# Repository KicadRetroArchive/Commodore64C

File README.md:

# Commodore 64C KiCad schematics

This project contains a series of schematics and PCB designs for the
Commodore 64C (aka C64-E) personal computer, redrawn in [KiCad](https://kicad.org/).

The schematic was extracted from images available from
[Bo Zimmerman's FTP site](http://www.zimmers.net/anonftp/pub/cbm/schematics/computers/c64/index.html).

The images are also available in the documentation directory.

The project is structured in three main folders:

- [250469-RevA](250469-RevA) - Revision A of the motherboard. This version is also known as
  _Short Board_ and sports the 64 pin _"Super PLA"_ (code 251715-01).
- [250469-RevB](250469-RevB) - Revision B of the motherboard. This version has
  a more advanced version of the Super PLA (code 252535-01) that integrates the Color RAM.
- [docs](docs) - Documentation.
- [libs](libs) - Project's specific KiCad libraries.

## References

- Schematics from [Zimmers FTP site](http://www.zimmers.net/anonftp/pub/cbm/schematics/computers/c64/index.html).
- [C64C Service Manual](http://www.zimmers.net/anonftp/pub/cbm/schematics/computers/c64/servicemanuals/C64-C64C_Service_Manual_314001-03_%281992_Mar%29.pdf).
- [Hardware information](https://www.c64-wiki.com/wiki/Portal:Hardware) from the C64-Wiki.

## Differences

While designing the schematics, I decided to consider the availability of all the
components used as a top priority. While there's little I can do for many of the
ICs, many other components can still be sourced from distributors today.

A few regular components are, however, impossible to find now. In these cases
I replaced them with the closest substitute I could find that is widely available.
These components are different from the originals:

- `CR2`: Diode Rectifier Bridge
- `L3,L4`: RF Choke Coils
- Some transistors and diodes

## KiCad libraries

Both subprojects use two KiCad set of libraries:

- The [KiCad Retro Library](https://github.com/KicadRetroArchive/kicad-retro-library).
- Project-specific libraries located in the [libs](libs) directory.
  - `C64-C-250469.kicad_sym` - C64C specific symbols.
  - `C64-C-250469.pretty` - C64C specific footprints.

> The project-specific libraries are located in a directory **above** the actual
> KiCad project. They are referenced through the `KIPRJMOD` environment variable
> in this way: `"${KIPRJMOD}/../libs/<name of library>"`.

## Credits

This project has been heavily inspired by these awesome projects:

- [LittleSixteen](https://github.com/SukkoPera/LittleSixteen) - Clone of the Commodore 16 by [@SukkoPera](https://github.com/SukkoPera).
- [Commodore-Plus4](https://github.com/StormTrooper/Commodore-Plus4) - Clone of the Commodore Plus 4 by [@StormTrooper](https://github.com/StormTrooper).
- [KU-14194HB-RevB-KiCad](https://github.com/bwack/KU-14194HB-RevB-KiCad) - Clone of the Commodore 64, Assy KU-14194HB-RevB by [@bwack](https://github.com/bwack).

## Contributing

We gladly accept contributions via GitHub pull requests. Please see
[CONTRIBUTING.md](CONTRIBUTING.md) for more details.

## License

Original schematic drawings and service manual are &copy; Commodore Electronics Ltd.

All KiCad design files are copyright &copy; 2020 Andrea Cisternino.

This project is Open Hardware licensed under the
[CERN-OHL-S v2](https://ohwr.org/project/cernohl/wikis/Documents/CERN-OHL-version-2)
license.

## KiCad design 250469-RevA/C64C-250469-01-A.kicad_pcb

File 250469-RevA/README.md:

# Assembly 250469 Rev. A

Original board:

(_From the [C64-Wiki](https://www.c64-wiki.com/wiki/Motherboard)_)

## Files

- Schematics in PDF: [C64C-250469-01-A.pdf](C64C-250469-01-A.pdf)
- Complete BOM in LibreOffice Calc format, including part numbers from Digi-Key and Mouser
  [C64C-250469-01-A.ods](C64C-250469-01-A.ods)

## Status

I am quite confident that the schematic is stable and bug-free.

**Good News!** I acquired a spare motherboard that matches exactly this revision.
With this example in my hand, I corrected all dimensional errors in the PCB.
I also placed with great precision all the external connectors.
Now work on routing the PCB can begin!

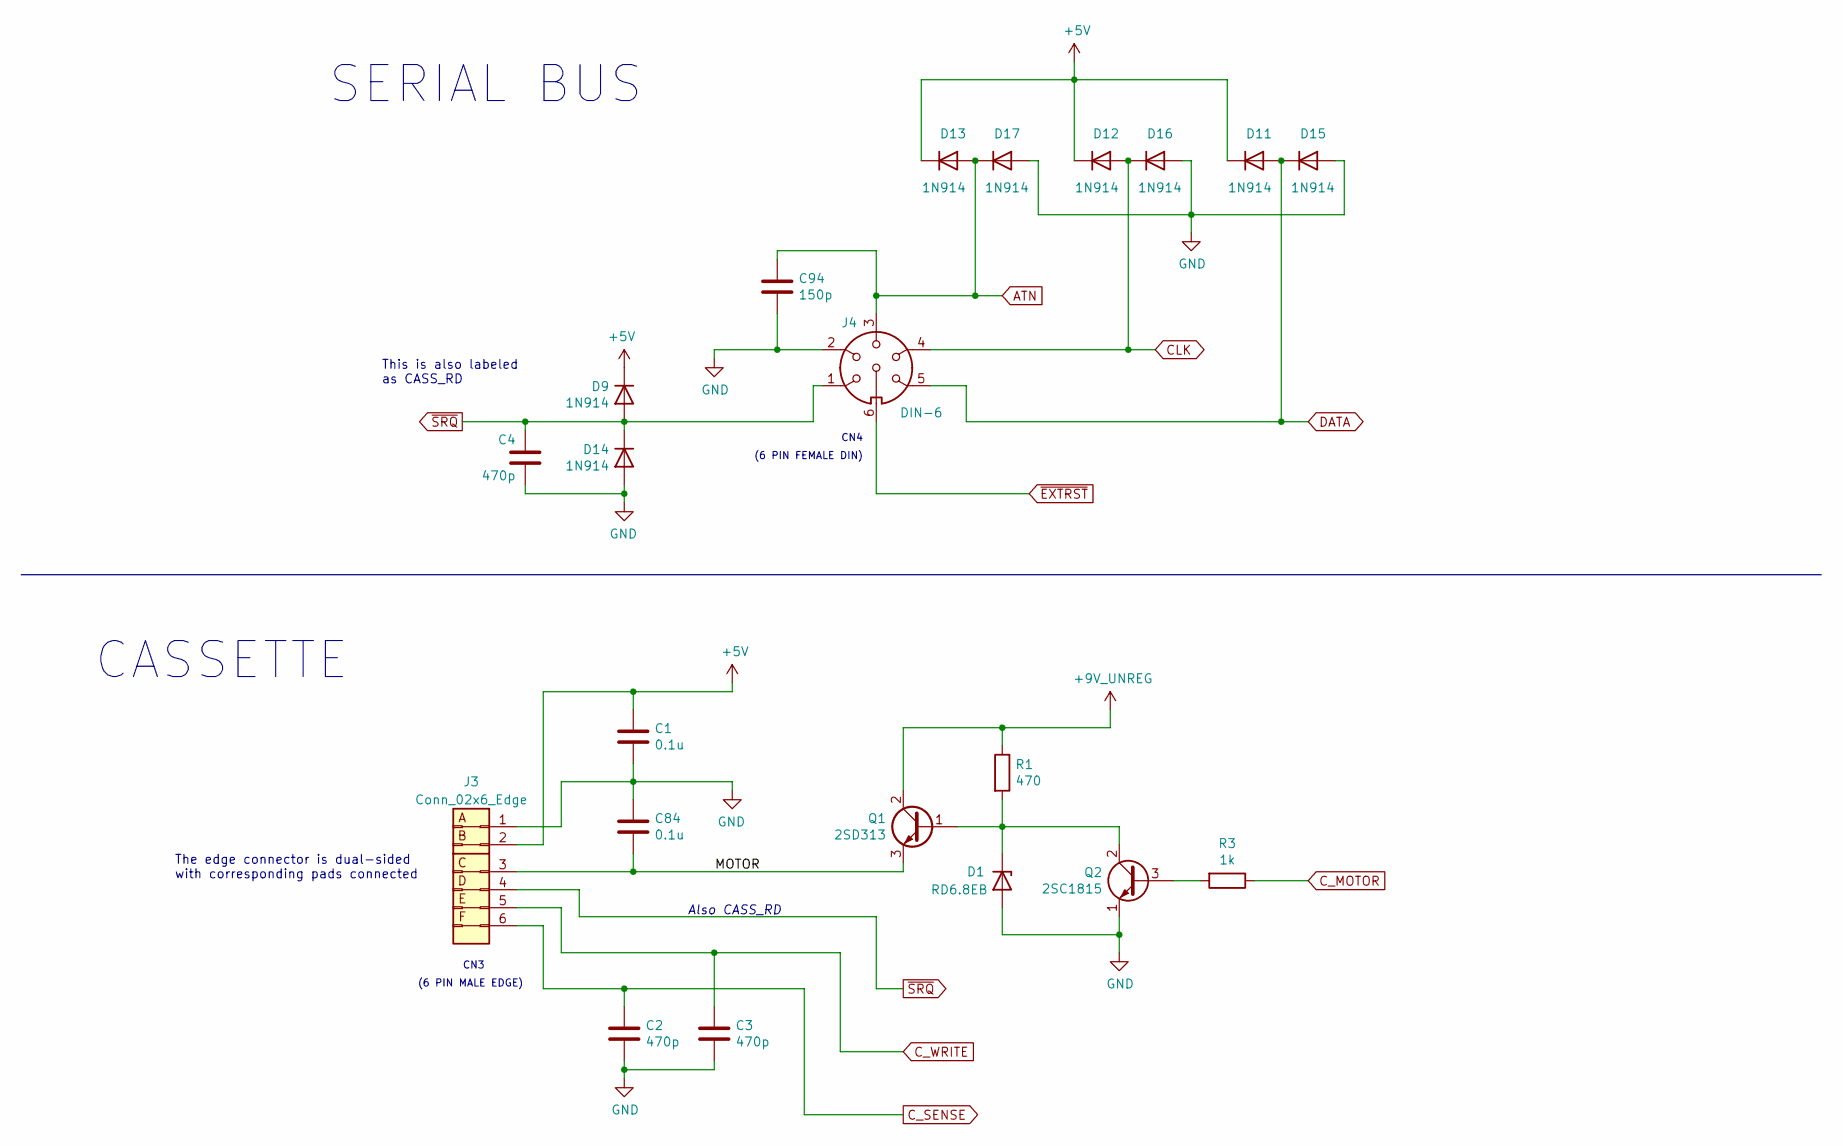
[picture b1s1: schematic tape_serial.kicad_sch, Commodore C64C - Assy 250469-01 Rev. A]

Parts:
C1, C84: 0.1u; C_Disc_D4.7mm_W2.5mm_P5.00mm
C2, C3, C4: 470p; C_Disc_D4.7mm_W2.5mm_P5.00mm
C94: 150p; C_Disc_D4.7mm_W2.5mm_P5.00mm
D1: RD6.8EB; D_DO-35_SOD27_P7.62mm_Horizontal
D9, D11, D12, D13, D14, D15, D16, D17: 1N914; D_DO-35_SOD27_P7.62mm_Horizontal
J3: Conn_02x6_Edge; Connector_Edge_2x6_P3.96mm
J4: DIN-6; C64_Original_DIN-6_Circular
Q1: 2SD313; TO-220-3_Vertical
Q2: 2SC1815; TO-92_Inline
R1: 470; R_Axial_DIN0309_L9.0mm_D3.2mm_P15.24mm_Horizontal
R3: 1k; R_Axial_DIN0207_L6.3mm_D2.5mm_P5.08mm_Vertical

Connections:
+5V: C1.1, D9.1 (K), D11.1 (K), D12.1 (K), D13.1 (K), J3.2, J3.B; also elsewhere on the board
+9V_UNREG: Q1.2 (C), R1.1; also elsewhere on the board
/Tape - Serial/MOTOR: C84.2, J3.3, Q1.3 (E)
ATN: C94.1, D13.2 (A), D17.1 (K), J4.3; also elsewhere on the board
CLK: D12.2 (A), D16.1 (K), J4.4; also elsewhere on the board
C_MOTOR: R3.1; also elsewhere on the board
C_SENSE: C2.1, J3.6; also elsewhere on the board
C_WRITE: C3.1, J3.5; also elsewhere on the board
DATA: D11.2 (A), D15.1 (K), J4.5; also elsewhere on the board
GND: C1.2, C2.2, C3.2, C4.2, C84.1, C94.2, D1.2 (A), D14.2 (A), D15.2 (A), D16.2 (A), D17.2 (A), J3.1, J4.0, J4.2, Q2.1 (E); also elsewhere on the board
unnamed: D1.1 (K), Q1.1 (B), Q2.2 (C), R1.2
unnamed: Q2.3 (B), R3.2
~EXTRST: J4.6; also elsewhere on the board
~SRQ: C4.1, D9.2 (A), D14.1 (K), J3.4, J3.D, J4.1; also elsewhere on the board

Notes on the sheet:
CN3
(6 PIN MALE EDGE)
Also CASS_RD
CN4
(6 PIN FEMALE DIN)
CASSETTE
The edge connector is dual-sided with corresponding pads connected
SERIAL BUS
This is also labeled as CASS_RD

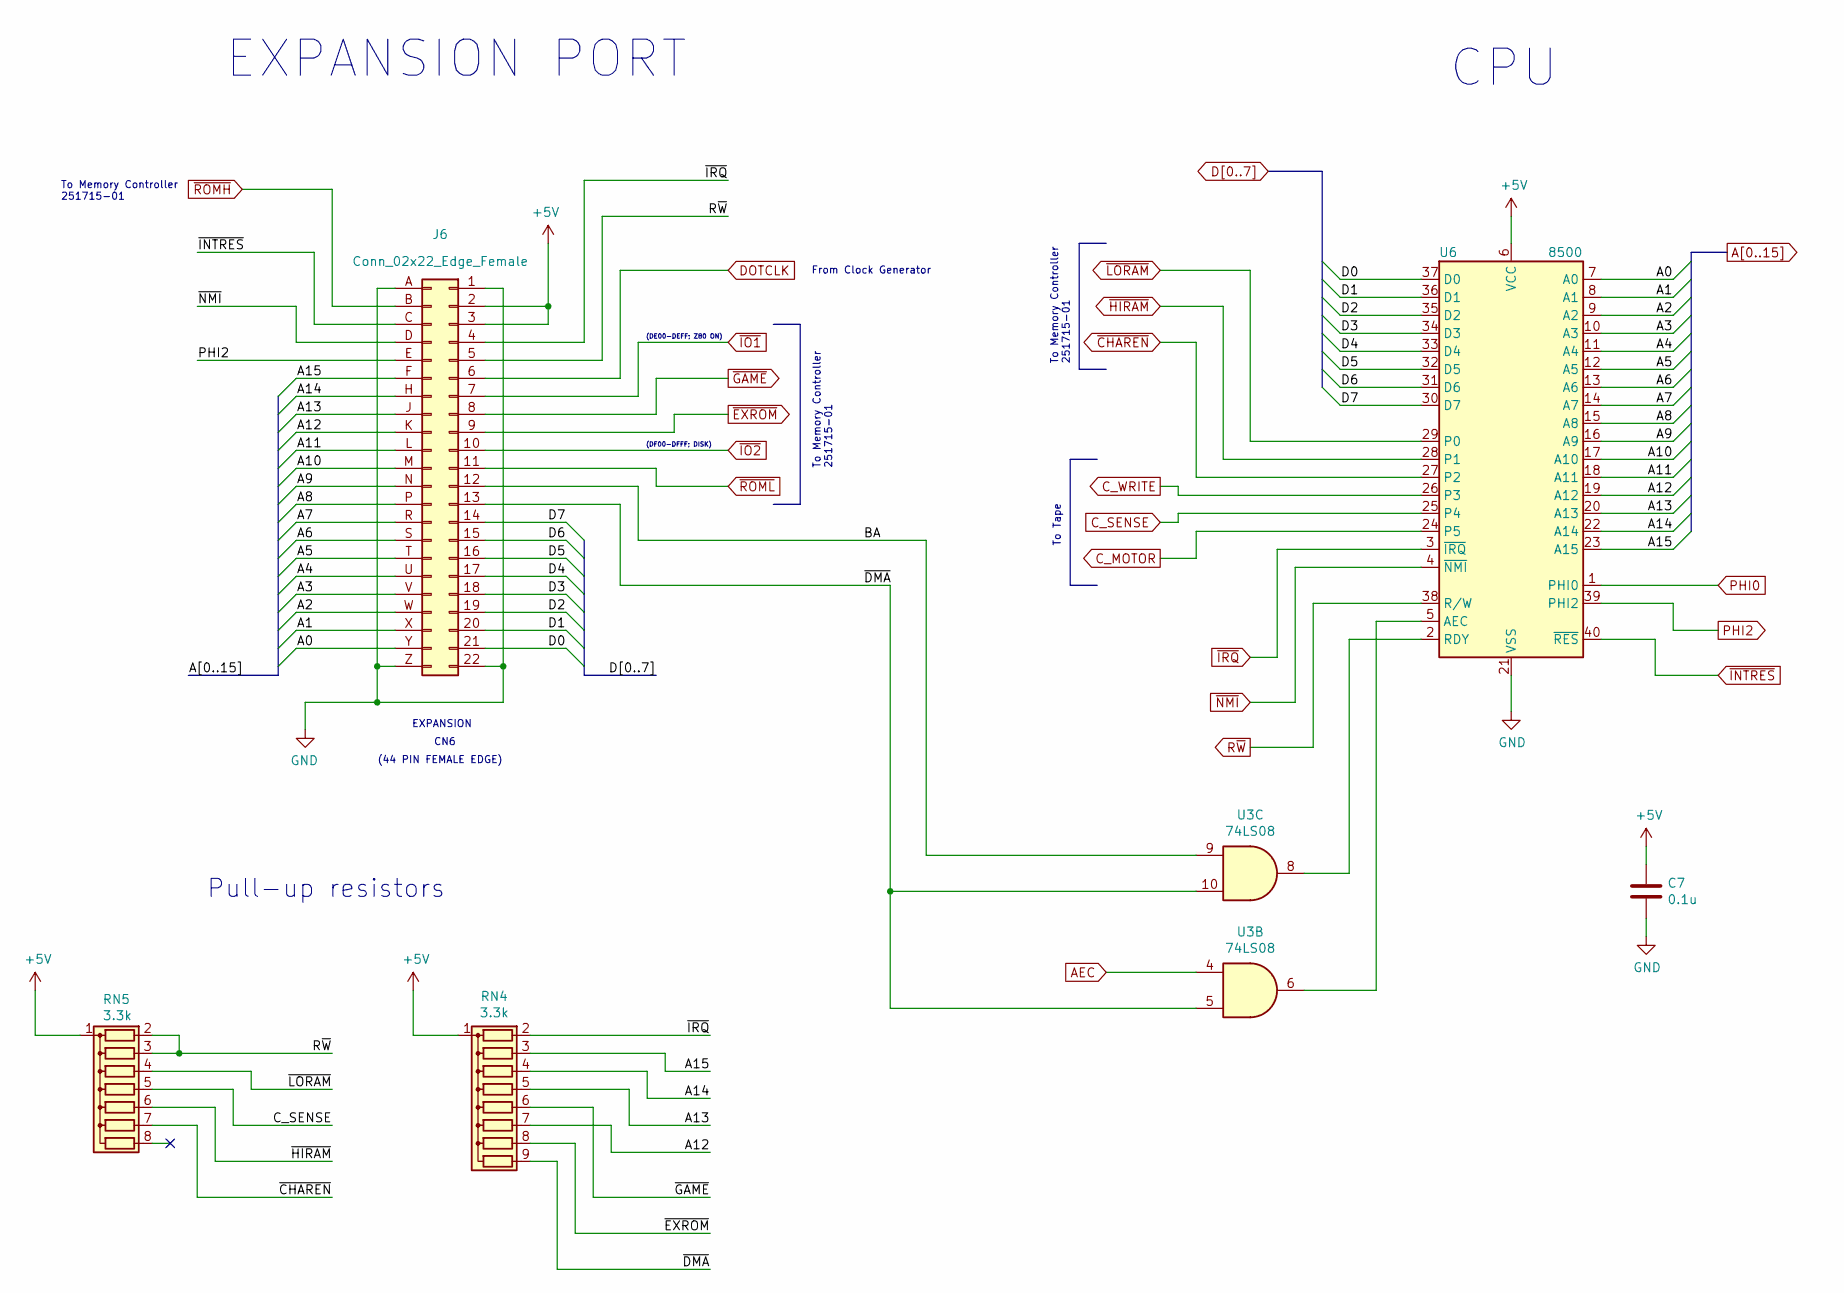
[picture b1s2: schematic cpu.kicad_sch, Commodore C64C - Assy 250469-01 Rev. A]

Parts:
C7: 0.1u; C_Disc_D4.7mm_W2.5mm_P5.00mm
J6: Conn_02x22_Edge_Female; Sullins_EBC22DRAN
RN4: 3.3k; R_Array_SIP9
RN5: 3.3k; R_Array_SIP8
U3: 74LS08; DIP-14_W7.62mm_Socket
U6: 8500; DIP-40_W15.24mm_Socket

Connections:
+5V: C7.1, J6.2, J6.3, RN4.1 (common), RN5.1 (common), U6.6 (VCC); also elsewhere on the board
/CPU - Expansion Port/BA: J6.12, U3.9
/CPU - Expansion Port/~DMA: J6.13, RN4.9 (R8), U3.5, U3.10
A0: J6.Y, U6.7 (A0); also elsewhere on the board
A1: J6.X, U6.8 (A1); also elsewhere on the board
A2: J6.W, U6.9 (A2); also elsewhere on the board
A3: J6.V, U6.10 (A3); also elsewhere on the board
A4: J6.U, U6.11 (A4); also elsewhere on the board
A5: J6.T, U6.12 (A5); also elsewhere on the board
A6: J6.S, U6.13 (A6); also elsewhere on the board
A7: J6.R, U6.14 (A7); also elsewhere on the board
A8: J6.P, U6.15 (A8); also elsewhere on the board
A9: J6.N, U6.16 (A9); also elsewhere on the board
A10: J6.M, U6.17 (A10); also elsewhere on the board
A11: J6.L, U6.18 (A11); also elsewhere on the board
A12: J6.K, RN4.7 (R6), U6.19 (A12); also elsewhere on the board
A13: J6.J, RN4.5 (R4), U6.20 (A13); also elsewhere on the board
A14: J6.H, RN4.4 (R3), U6.22 (A14); also elsewhere on the board
A15: J6.F, RN4.3 (R2), U6.23 (A15); also elsewhere on the board
AEC: U3.4; also elsewhere on the board
C_MOTOR: U6.24 (P5); also elsewhere on the board
C_SENSE: RN5.5 (R4), U6.25 (P4); also elsewhere on the board
C_WRITE: U6.26 (P3); also elsewhere on the board
D0: J6.21, U6.37 (D0); also elsewhere on the board
D1: J6.20, U6.36 (D1); also elsewhere on the board
D2: J6.19, U6.35 (D2); also elsewhere on the board
D3: J6.18, U6.34 (D3); also elsewhere on the board
D4: J6.17, U6.33 (D4); also elsewhere on the board
D5: J6.16, U6.32 (D5); also elsewhere on the board
D6: J6.15, U6.31 (D6); also elsewhere on the board
D7: J6.14, U6.30 (D7); also elsewhere on the board
DOTCLK: J6.6; also elsewhere on the board
GND: C7.2, J6.1, J6.22, J6.A, J6.Z, U6.21 (VSS); also elsewhere on the board
unnamed: U3.6, U6.5 (AEC)
unnamed: U3.8, U6.2 (RDY)
PHI0: U6.1 (PHI0); also elsewhere on the board
PHI2: J6.E, U6.39 (PHI2); also elsewhere on the board
R~W: J6.5, RN5.2 (R1), RN5.3 (R2), U6.38 (R/W); also elsewhere on the board
~CHAREN: RN5.7 (R6), U6.27 (P2); also elsewhere on the board
~EXROM: J6.9, RN4.8 (R7); also elsewhere on the board
~GAME: J6.8, RN4.6 (R5); also elsewhere on the board
~HIRAM: RN5.6 (R5), U6.28 (P1); also elsewhere on the board
~INTRES: J6.C, U6.40 (~RES); also elsewhere on the board
~IO1: J6.7; also elsewhere on the board
~IO2: J6.10; also elsewhere on the board
~IRQ: J6.4, RN4.2 (R1), U6.3 (~IRQ); also elsewhere on the board
~LORAM: RN5.4 (R3), U6.29 (P0); also elsewhere on the board
~NMI: J6.D, U6.4 (~NMI); also elsewhere on the board
~ROMH: J6.B; also elsewhere on the board
~ROML: J6.11; also elsewhere on the board

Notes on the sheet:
To Tape
(DE00-DEFF; Z80 ON)
EXPANSION
Pull-up resistors
(44 PIN FEMALE EDGE)
CN6
EXPANSION PORT
CPU
To Memory Controller 251715-01
From Clock Generator
(DF00-DFFF; DISK)

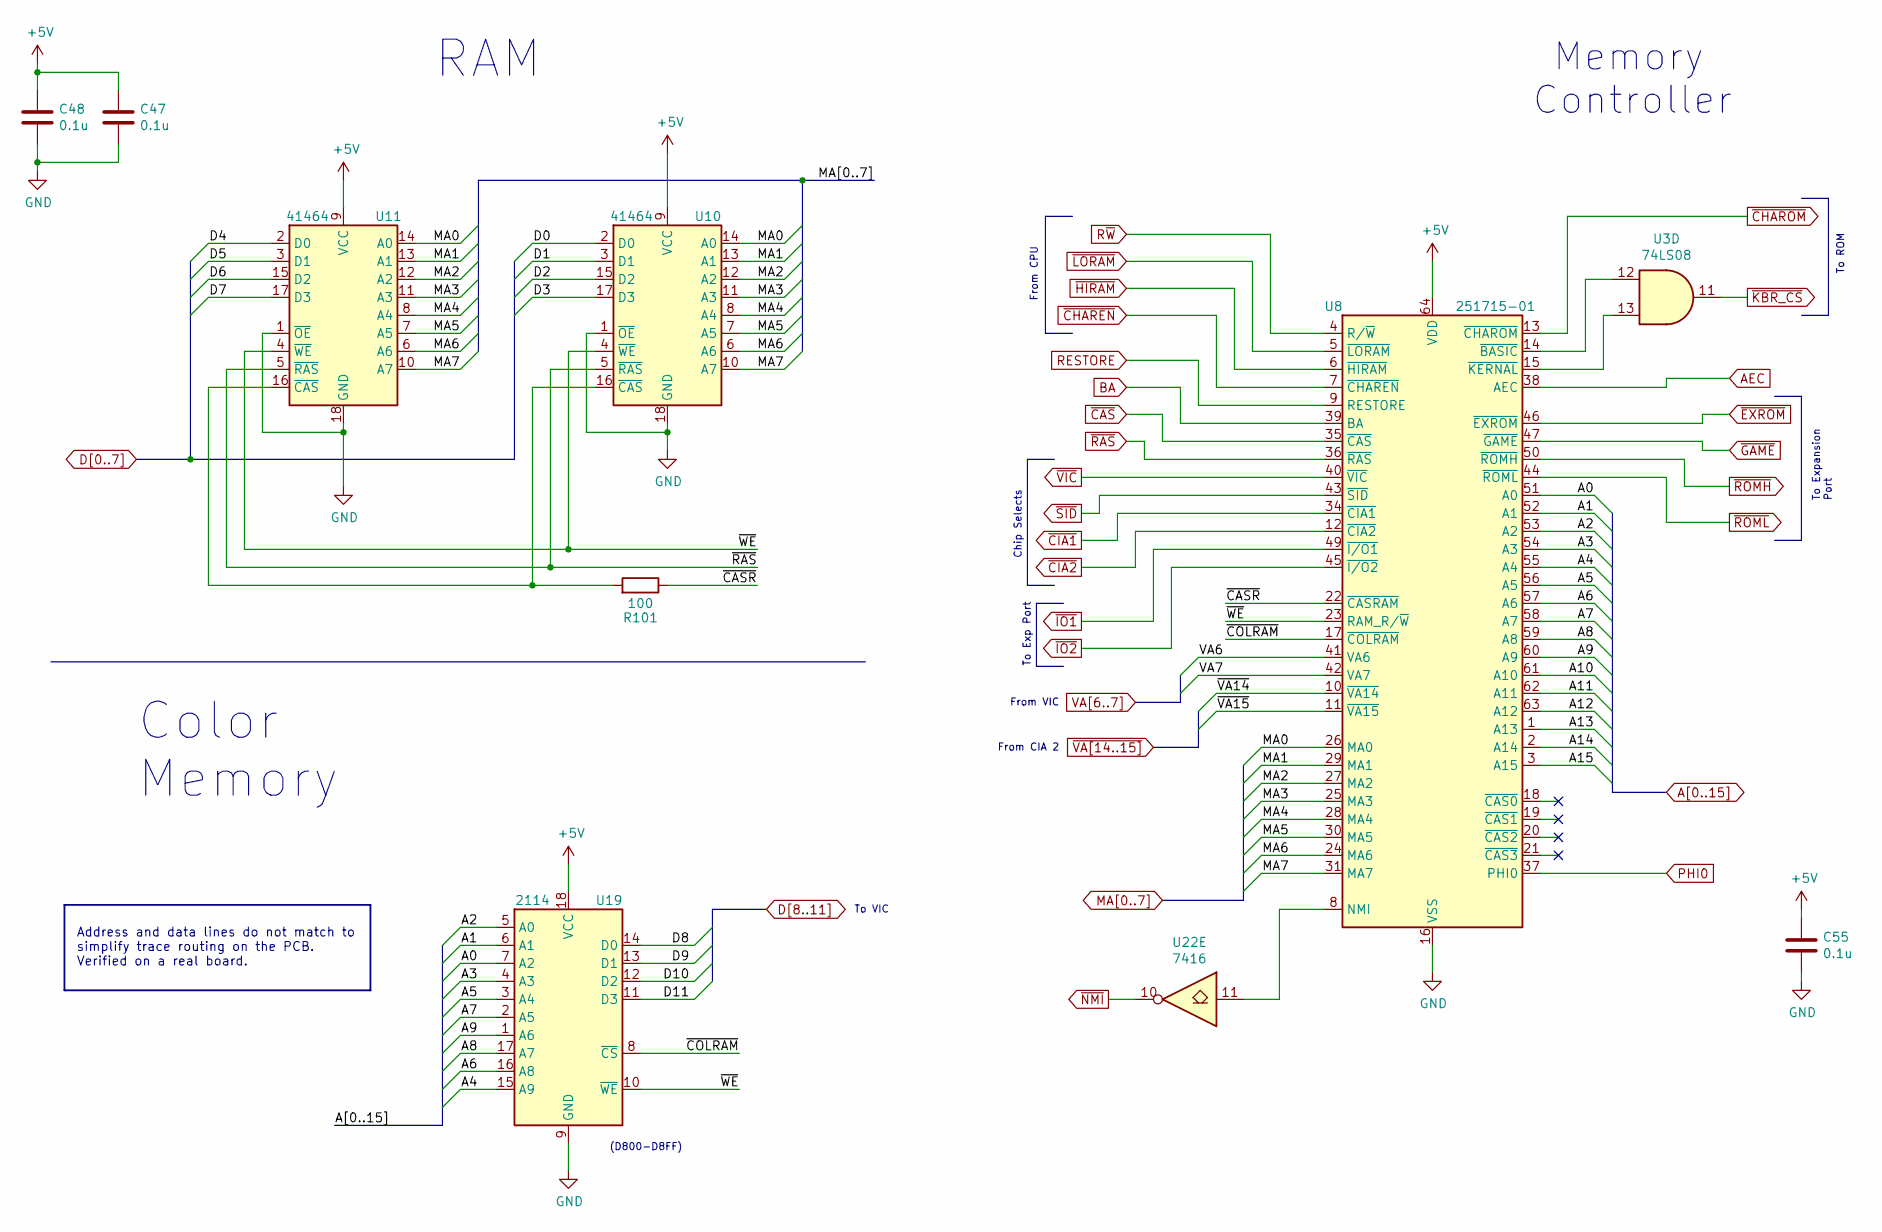
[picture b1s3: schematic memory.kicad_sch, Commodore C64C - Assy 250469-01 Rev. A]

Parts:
C47, C48, C55: 0.1u; C_Disc_D4.7mm_W2.5mm_P5.00mm
R101: 100; R_Axial_DIN0207_L6.3mm_D2.5mm_P5.08mm_Vertical
U3: 74LS08; DIP-14_W7.62mm_Socket
U8: 251715-01; SPDIP-64_W19.05mm_Socket_LongPads
U10, U11: 41464; DIP-18_W7.62mm_Socket
U19: 2114; DIP-18_W7.62mm_Socket
U22: 7416; DIP-14_W7.62mm_Socket

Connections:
+5V: C47.1, C48.1, C55.1, U8.64 (VDD), U10.9 (VCC), U11.9 (VCC), U19.18 (VCC); also elsewhere on the board
/Memory Controller - RAM/~CASR: R101.1, U8.22 (~CASRAM)
/Memory Controller - RAM/~COLRAM: U8.17 (~COLRAM), U19.8 (~CS)
/Memory Controller - RAM/~WE: U8.23 (RAM_R/~W), U10.4 (~WE), U11.4 (~WE), U19.10 (~WE)
A0: U8.51 (A0), U19.7 (A2); also elsewhere on the board
A1: U8.52 (A1), U19.6 (A1); also elsewhere on the board
A2: U8.53 (A2), U19.5 (A0); also elsewhere on the board
A3: U8.54 (A3), U19.4 (A3); also elsewhere on the board
A4: U8.55 (A4), U19.15 (A9); also elsewhere on the board
A5: U8.56 (A5), U19.3 (A4); also elsewhere on the board
A6: U8.57 (A6), U19.16 (A8); also elsewhere on the board
A7: U8.58 (A7), U19.2 (A5); also elsewhere on the board
A8: U8.59 (A8), U19.17 (A7); also elsewhere on the board
A9: U8.60 (A9), U19.1 (A6); also elsewhere on the board
A10: U8.61 (A10); also elsewhere on the board
A11: U8.62 (A11); also elsewhere on the board
A12: U8.63 (A12); also elsewhere on the board
A13: U8.1 (A13); also elsewhere on the board
A14: U8.2 (A14); also elsewhere on the board
A15: U8.3 (A15); also elsewhere on the board
AEC: U8.38 (AEC); also elsewhere on the board
BA: U8.39 (BA); also elsewhere on the board
D0: U10.2 (D0); also elsewhere on the board
D1: U10.3 (D1); also elsewhere on the board
D2: U10.15 (D2); also elsewhere on the board
D3: U10.17 (D3); also elsewhere on the board
D4: U11.2 (D0); also elsewhere on the board
D5: U11.3 (D1); also elsewhere on the board
D6: U11.15 (D2); also elsewhere on the board
D7: U11.17 (D3); also elsewhere on the board
D8: U19.14 (D0); also elsewhere on the board
D9: U19.13 (D1); also elsewhere on the board
D10: U19.12 (D2); also elsewhere on the board
D11: U19.11 (D3); also elsewhere on the board
GND: C47.2, C48.2, C55.2, U8.16 (VSS), U8.33 (VSS), U8.48 (VSS), U10.1 (~OE), U10.18 (GND), U11.1 (~OE), U11.18 (GND), U19.9 (GND); also elsewhere on the board
MA0: U8.26 (MA0), U10.14 (A0), U11.14 (A0); also elsewhere on the board
MA1: U8.29 (MA1), U10.13 (A1), U11.13 (A1); also elsewhere on the board
MA2: U8.27 (MA2), U10.12 (A2), U11.12 (A2); also elsewhere on the board
MA3: U8.25 (MA3), U10.11 (A3), U11.11 (A3); also elsewhere on the board
MA4: U8.28 (MA4), U10.8 (A4), U11.8 (A4); also elsewhere on the board
MA5: U8.30 (MA5), U10.7 (A5), U11.7 (A5); also elsewhere on the board
MA6: U8.24 (MA6), U10.6 (A6), U11.6 (A6)
MA7: U8.31 (MA7), U10.10 (A7), U11.10 (A7)
unnamed: R101.2, U10.16 (~CAS), U11.16 (~CAS)
unnamed: U3.12, U8.14 (~BASIC)
unnamed: U3.13, U8.15 (~KERNAL)
unnamed: U8.8 (NMI), U22.11
PHI0: U8.37 (PHI0); also elsewhere on the board
RESTORE: U8.9 (RESTORE); also elsewhere on the board
R~W: U8.4 (R/~W); also elsewhere on the board
VA6: U8.41 (VA6); also elsewhere on the board
VA7: U8.42 (VA7); also elsewhere on the board
~CAS: U8.35 (~CAS); also elsewhere on the board
~CHAREN: U8.7 (~CHAREN); also elsewhere on the board
~CHAROM: U8.13 (~CHAROM); also elsewhere on the board
~CIA1: U8.34 (~CIA1); also elsewhere on the board
~CIA2: U8.12 (~CIA2); also elsewhere on the board
~EXROM: U8.46 (~EXROM); also elsewhere on the board
~GAME: U8.47 (~GAME); also elsewhere on the board
~HIRAM: U8.6 (~HIRAM); also elsewhere on the board
~IO1: U8.49 (~I/O1); also elsewhere on the board
~IO2: U8.45 (~I/O2); also elsewhere on the board
~KBR_CS: U3.11; also elsewhere on the board
~LORAM: U8.5 (~LORAM); also elsewhere on the board
~NMI: U22.10; also elsewhere on the board
~RAS: U8.36 (~RAS), U10.5 (~RAS), U11.5 (~RAS); also elsewhere on the board
~ROMH: U8.50 (~ROMH); also elsewhere on the board
~ROML: U8.44 (~ROML); also elsewhere on the board
~SID: U8.43 (~SID); also elsewhere on the board
~VA14: U8.10 (~VA14); also elsewhere on the board
~VA15: U8.11 (~VA15); also elsewhere on the board
~VIC: U8.40 (~VIC); also elsewhere on the board

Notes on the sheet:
To Expansion Port
RAM
To Exp Port
To ROM
Address and data lines do not match to simplify trace routing on the PCB. Verified on a real board.
From CIA 2
From VIC
(D800-D8FF)
From CPU
Color Memory
Memory Controller
Chip Selects
To VIC

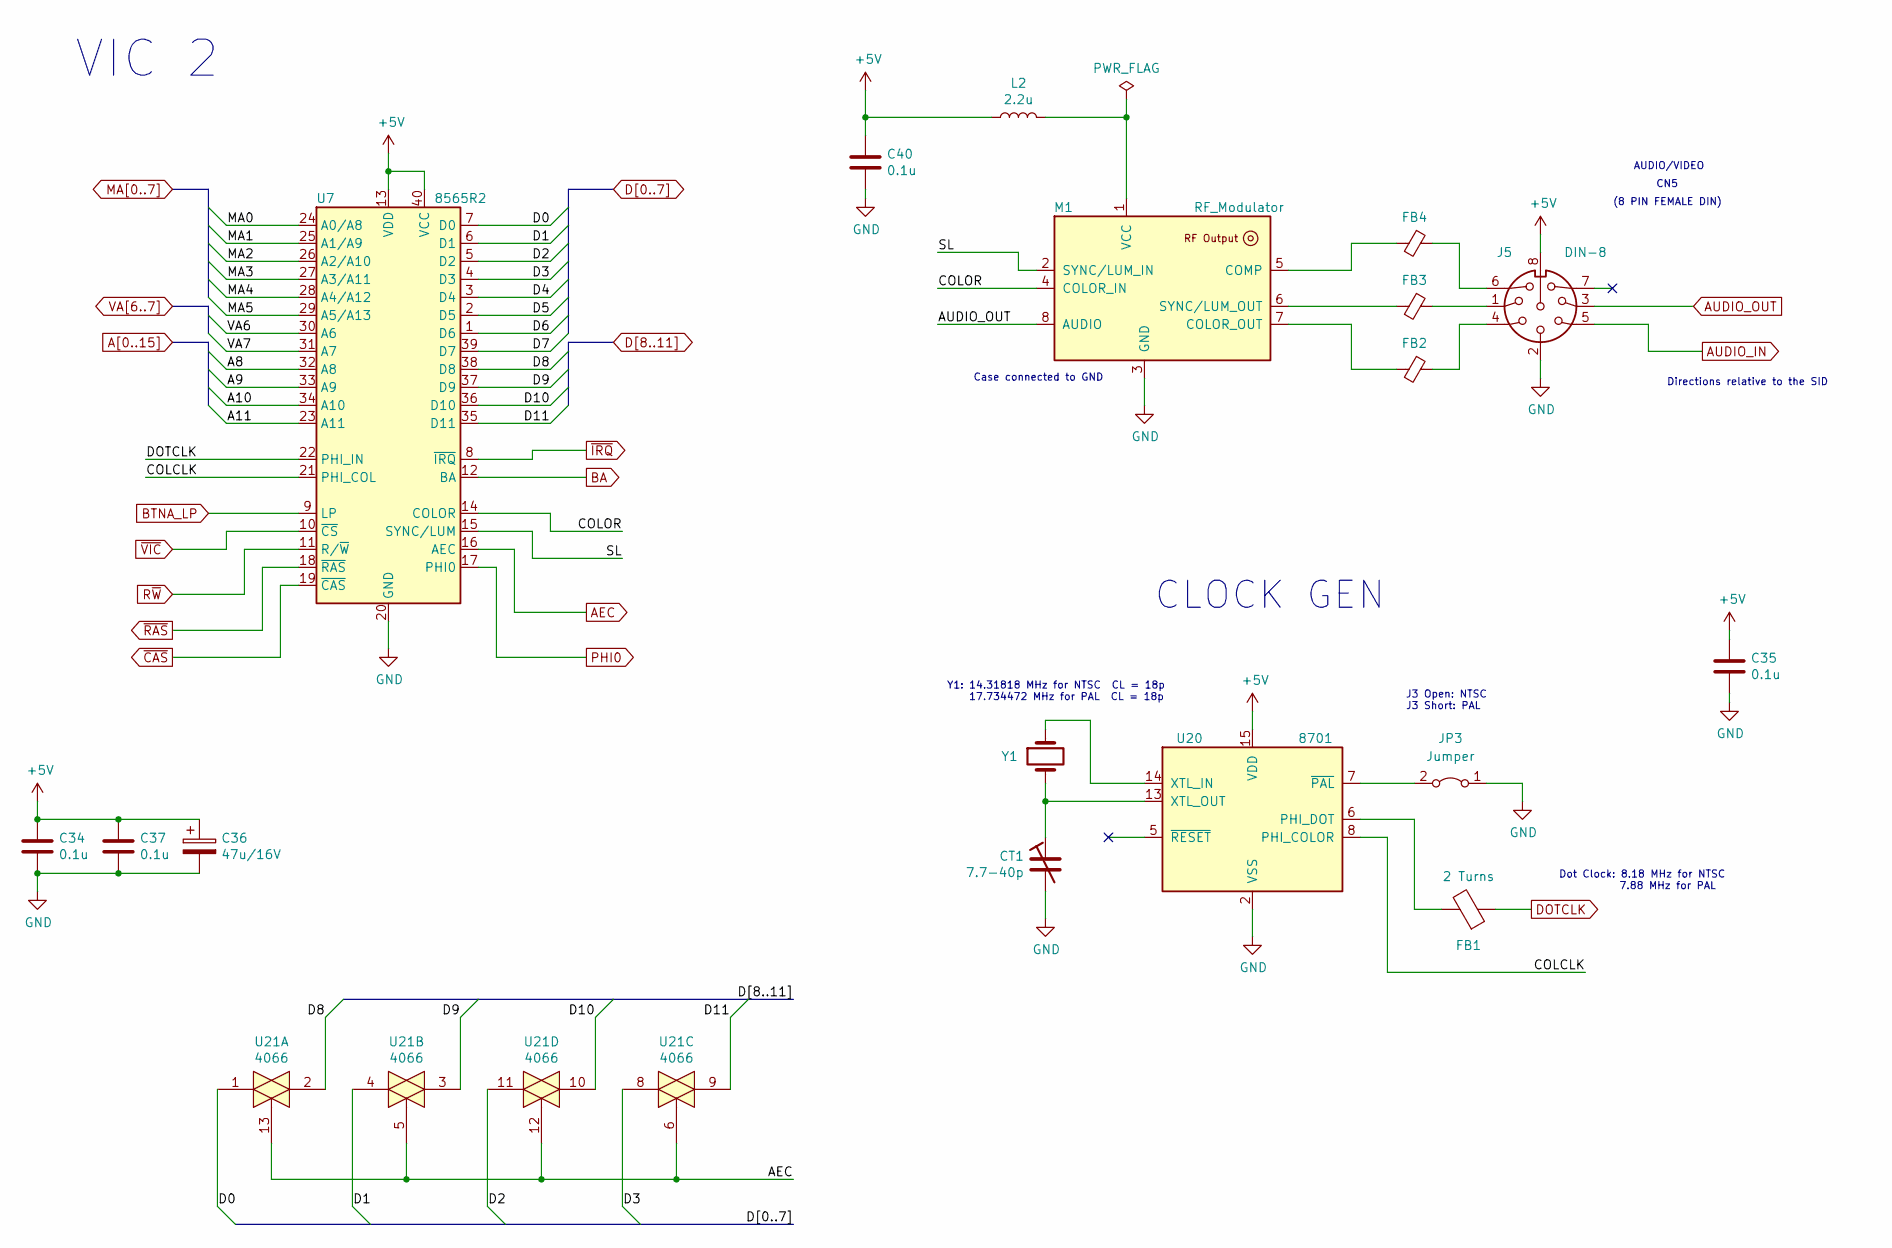
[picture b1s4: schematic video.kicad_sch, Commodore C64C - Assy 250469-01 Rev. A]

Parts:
C34, C35, C37, C40: 0.1u; C_Disc_D4.7mm_W2.5mm_P5.00mm
C36: 47u/16V; CP_Radial_D8.0mm_P5.00mm
CT1: 7.7-40p; C_Trimmer_JML_JML06_P5mm
FB1: 2 Turns; L_Axial_Dual_L7.0mm_D3.3mm_P5.08mm_Vertical
FB2, FB3, FB4: Ferrite_Bead_Small; L_Axial_L7.0mm_D3.3mm_P5.08mm_Vertical_Fastron_MICC
J5: DIN-8; C64_Original_DIN-8_Circular
JP3: Jumper; PinHeader_1x02_P2.54mm_Vertical
L2: 2.2u; L_Axial_L9.5mm_D4.0mm_P15.24mm_Horizontal_Fastron_SMCC
M1: RF_Modulator
U7: 8565R2; DIP-40_W15.24mm_Socket
U20: 8701; DIP-16_W7.62mm_Socket
U21: 4066; DIP-14_W7.62mm_Socket
Y1: Crystal; Crystal_HC49-U_Vertical

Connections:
+5V: C34.1, C35.1, C36.1, C37.1, C40.1, J5.8, L2.1, U7.13 (VDD), U7.40 (VCC), U20.12 (VDD), U20.15 (VDD); also elsewhere on the board
/Video - ClockGen/COLCLK: U7.21 (PHI_COL), U20.8 (PHI_COLOR)
/Video - ClockGen/COLOR: M1.4 (COLOR_IN), U7.14 (COLOR)
/Video - ClockGen/SL: M1.2 (SYNC/LUM_IN), U7.15 (SYNC/LUM)
A8: U7.32 (A8); also elsewhere on the board
A9: U7.33 (A9); also elsewhere on the board
A10: U7.34 (A10); also elsewhere on the board
A11: U7.23 (A11); also elsewhere on the board
AEC: U7.16 (AEC), U21.5, U21.6, U21.12, U21.13; also elsewhere on the board
AUDIO_IN: J5.5; also elsewhere on the board
AUDIO_OUT: J5.3, M1.8 (AUDIO); also elsewhere on the board
BA: U7.12 (BA); also elsewhere on the board
BTNA_LP: U7.9 (LP); also elsewhere on the board
D0: U7.7 (D0), U21.1; also elsewhere on the board
D1: U7.6 (D1), U21.4; also elsewhere on the board
D2: U7.5 (D2), U21.11; also elsewhere on the board
D3: U7.4 (D3), U21.8; also elsewhere on the board
D4: U7.3 (D4); also elsewhere on the board
D5: U7.2 (D5); also elsewhere on the board
D6: U7.1 (D6); also elsewhere on the board
D7: U7.39 (D7); also elsewhere on the board
D8: U7.38 (D8), U21.2; also elsewhere on the board
D9: U7.37 (D9), U21.3; also elsewhere on the board
D10: U7.36 (D10), U21.10; also elsewhere on the board
D11: U7.35 (D11), U21.9; also elsewhere on the board
DOTCLK: FB1.1, U7.22 (PHI_IN); also elsewhere on the board
GND: C34.2, C35.2, C36.2, C37.2, C40.2, CT1.2, J5.0, J5.2, JP3.1 (A), M1.3 (GND), U7.20 (GND), U20.2 (VSS), U20.4, U20.9 (VSS); also elsewhere on the board
MA0: U7.24 (A0/A8); also elsewhere on the board
MA1: U7.25 (A1/A9); also elsewhere on the board
MA2: U7.26 (A2/A10); also elsewhere on the board
MA3: U7.27 (A3/A11); also elsewhere on the board
MA4: U7.28 (A4/A12); also elsewhere on the board
MA5: U7.29 (A5/A13); also elsewhere on the board
unnamed: CT1.1, U20.13 (XTL_OUT), Y1.2
unnamed: FB1.2, U20.6 (PHI_DOT)
unnamed: FB2.1, J5.4
unnamed: FB2.2, M1.7 (COLOR_OUT)
unnamed: FB3.1, J5.1
unnamed: FB3.2, M1.6 (SYNC/LUM_OUT)
unnamed: FB4.1, J5.6
unnamed: FB4.2, M1.5 (COMP)
unnamed: JP3.2 (B), U20.7 (~PAL)
unnamed: L2.2, M1.1 (VCC)
unnamed: U20.14 (XTL_IN), Y1.1
PHI0: U7.17 (PHI0); also elsewhere on the board
R~W: U7.11 (R/~W); also elsewhere on the board
VA6: U7.30 (A6); also elsewhere on the board
VA7: U7.31 (A7); also elsewhere on the board
~CAS: U7.19 (~CAS); also elsewhere on the board
~IRQ: U7.8 (~IRQ); also elsewhere on the board
~RAS: U7.18 (~RAS); also elsewhere on the board
~VIC: U7.10 (~CS); also elsewhere on the board

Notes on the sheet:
Case connected to GND
Directions relative to the SID
AUDIO/VIDEO
Dot Clock: 8.18 MHz for NTSC 7.88 MHz for PAL
Y1: 14.31818 MHz for NTSC CL = 18p 17.734472 MHz for PAL CL = 18p
CLOCK GEN
(8 PIN FEMALE DIN)
CN5
J3 Open: NTSC J3 Short: PAL
VIC 2

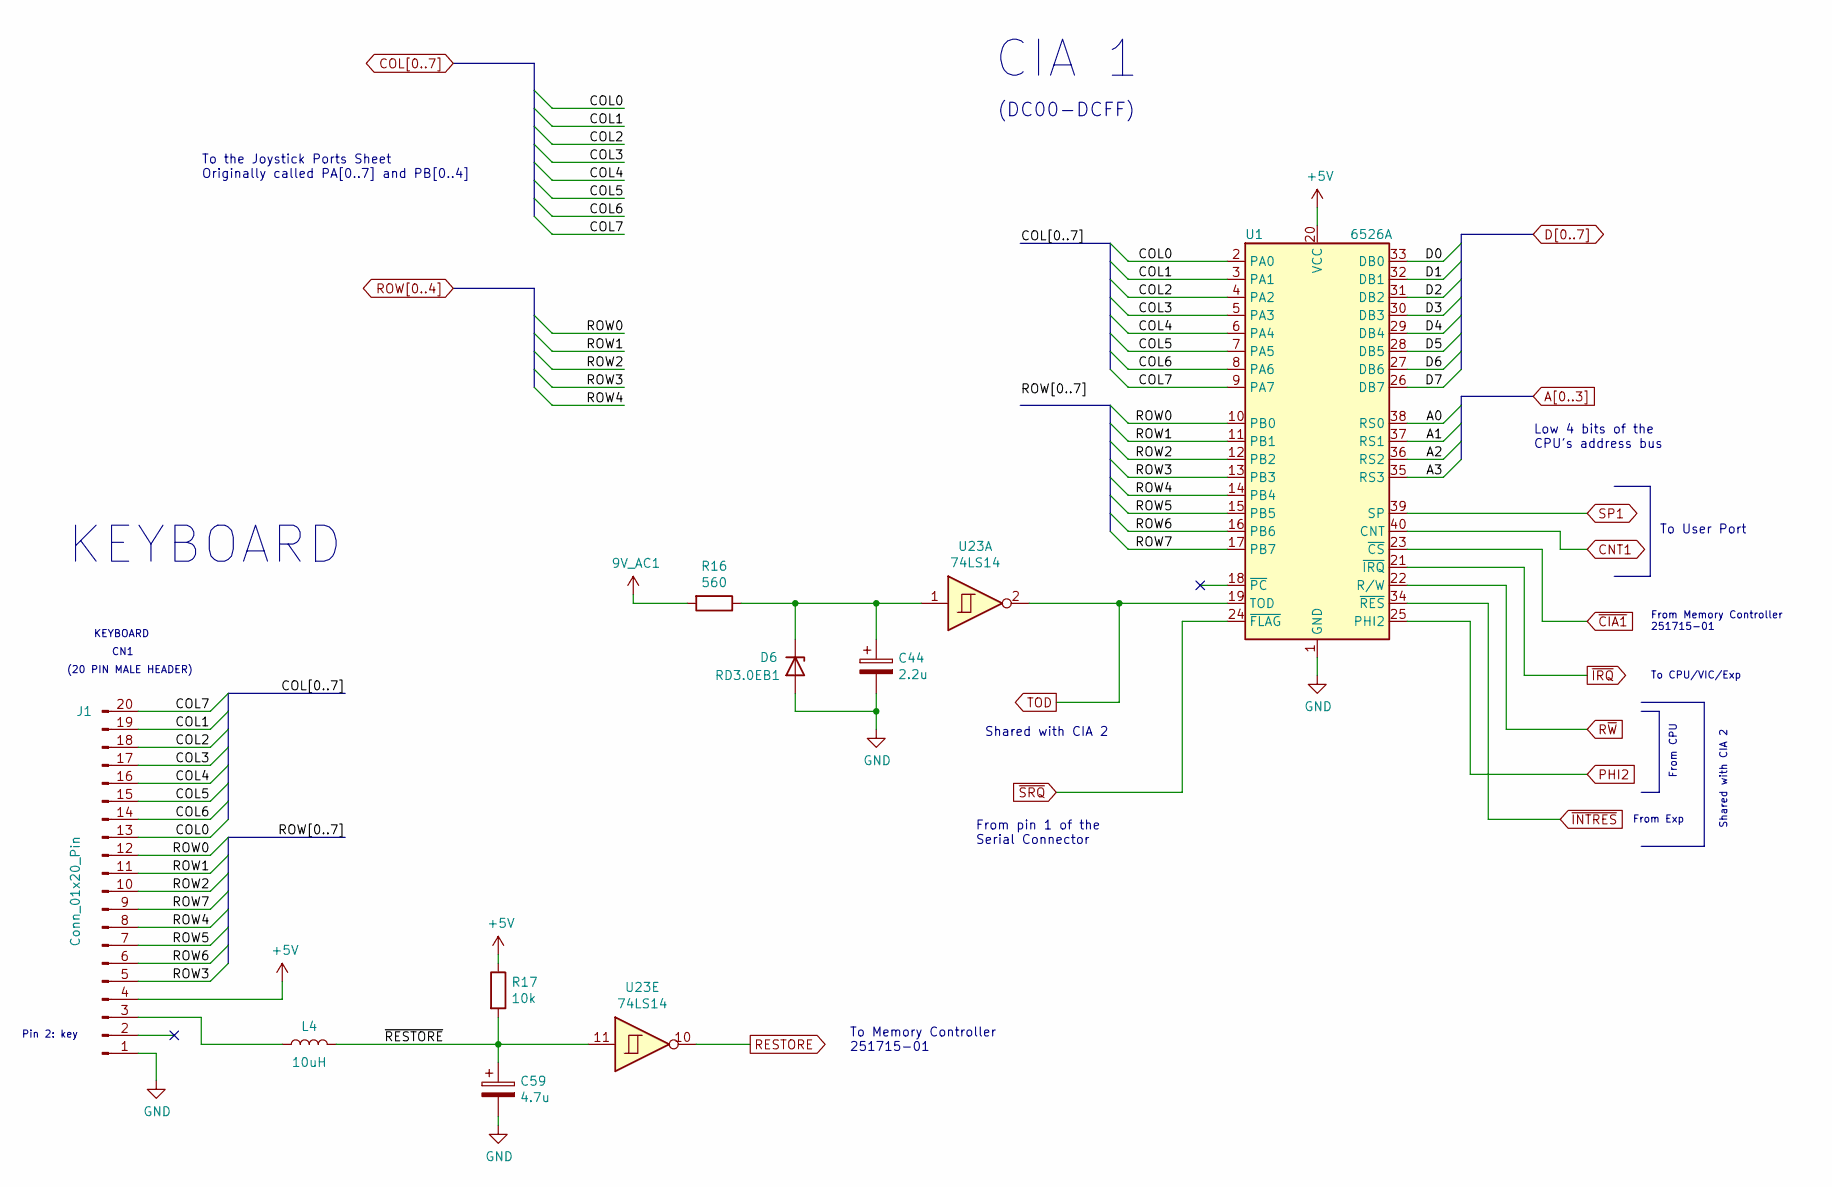
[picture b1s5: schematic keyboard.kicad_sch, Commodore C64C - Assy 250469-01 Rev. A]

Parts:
C44: 2.2u; CP_Radial_D8.0mm_P5.00mm
C59: 4.7u; CP_Radial_D8.0mm_P5.00mm
D6: RD3.0EB1; D_DO-35_SOD27_P7.62mm_Horizontal
J1: Conn_01x20_Pin; PinHeader_1x20_P2.54mm_Vertical
L4: 10uH; L_Radial_L7.5mm_W3mm_P5.00mm_Kemet_SBT-02
R16: 560; R_Axial_DIN0207_L6.3mm_D2.5mm_P5.08mm_Vertical
R17: 10k; R_Axial_DIN0207_L6.3mm_D2.5mm_P5.08mm_Vertical
U1: 6526A; DIP-40_W15.24mm_Socket
U23: 74LS14; DIP-14_W7.62mm_Socket

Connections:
9V_AC1: R16.2; also elsewhere on the board
+5V: J1.4, R17.1, U1.20 (VCC); also elsewhere on the board
/Keyboard - CIA 1/ROW5: J1.7, U1.15 (PB5)
/Keyboard - CIA 1/ROW6: J1.6, U1.16 (PB6)
/Keyboard - CIA 1/ROW7: J1.9, U1.17 (PB7)
/Keyboard - CIA 1/~RESTORE: C59.1, L4.2, R17.2, U23.11
A0: U1.38 (RS0); also elsewhere on the board
A1: U1.37 (RS1); also elsewhere on the board
A2: U1.36 (RS2); also elsewhere on the board
A3: U1.35 (RS3); also elsewhere on the board
CNT1: U1.40 (CNT); also elsewhere on the board
COL0: J1.13, U1.2 (PA0); also elsewhere on the board
COL1: J1.19, U1.3 (PA1); also elsewhere on the board
COL2: J1.18, U1.4 (PA2); also elsewhere on the board
COL3: J1.17, U1.5 (PA3); also elsewhere on the board
COL4: J1.16, U1.6 (PA4); also elsewhere on the board
COL5: J1.15, U1.7 (PA5)
COL6: J1.14, U1.8 (PA6); also elsewhere on the board
COL7: J1.20, U1.9 (PA7); also elsewhere on the board
D0: U1.33 (DB0); also elsewhere on the board
D1: U1.32 (DB1); also elsewhere on the board
D2: U1.31 (DB2); also elsewhere on the board
D3: U1.30 (DB3); also elsewhere on the board
D4: U1.29 (DB4); also elsewhere on the board
D5: U1.28 (DB5); also elsewhere on the board
D6: U1.27 (DB6); also elsewhere on the board
D7: U1.26 (DB7); also elsewhere on the board
GND: C44.2, C59.2, D6.2 (A), J1.1, U1.1 (GND); also elsewhere on the board
unnamed: C44.1, D6.1 (K), R16.1, U23.1
unnamed: J1.3, L4.1
PHI2: U1.25 (PHI2); also elsewhere on the board
RESTORE: U23.10; also elsewhere on the board
ROW0: J1.12, U1.10 (PB0); also elsewhere on the board
ROW1: J1.11, U1.11 (PB1); also elsewhere on the board
ROW2: J1.10, U1.12 (PB2); also elsewhere on the board
ROW3: J1.5, U1.13 (PB3); also elsewhere on the board
R~W: U1.22 (R/W); also elsewhere on the board
SP1: U1.39 (SP); also elsewhere on the board
TOD: U1.19 (TOD), U23.2; also elsewhere on the board
~CIA1: U1.23 (~CS); also elsewhere on the board
~INTRES: U1.34 (~RES); also elsewhere on the board
~IRQ: U1.21 (~IRQ); also elsewhere on the board
~SRQ: U1.24 (~FLAG); also elsewhere on the board

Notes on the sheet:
KEYBOARD
Shared with CIA 2
(DC00-DCFF)
To the Joystick Ports Sheet Originally called PA[0..7] and PB[0..4]
From Exp
From pin 1 of the Serial Connector
To Memory Controller 251715-01
(20 PIN MALE HEADER)
From CPU
Pin 2: key
To User Port
CN1
Low 4 bits of the CPU's address bus
To CPU/VIC/Exp
CIA 1
From Memory Controller 251715-01

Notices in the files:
250469-RevA/audio.kicad_sch:
KiCad schematic licensed under CERN-OHL-S
